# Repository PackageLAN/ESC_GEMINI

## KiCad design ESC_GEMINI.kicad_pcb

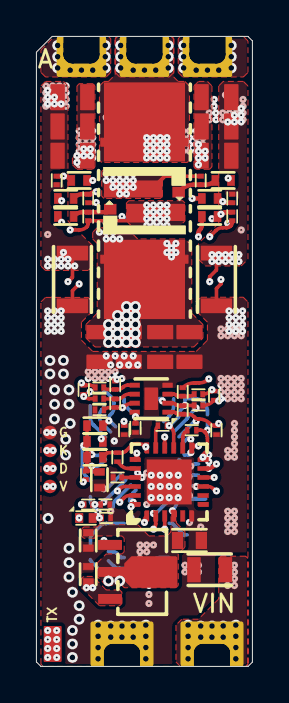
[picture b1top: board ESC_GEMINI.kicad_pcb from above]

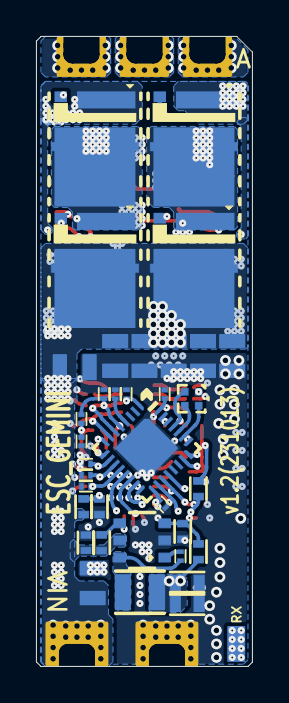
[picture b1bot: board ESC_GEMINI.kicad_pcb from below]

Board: 6 copper layers, 12.0 x 35.0 mm, 106 parts (36 on the bottom side), 57 nets.

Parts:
C1, C5, C6, C15, C48, C49: 100pF; C0201(0603M)
C2, C3, C4, C7, C8, C9, C10, C11, C12, C13, C14, C16, C24, C50, C51, C53, C54: 10uF; C0805(2012M)
C17, C19, C31, C46: 10nF; C0201(0603M)
C18, C20, C21, C22, C30, C45: 100nF; C0201(0603M)
C25, C28: 1uF; C0402(1005M)
C26: 100nF; C0402(1005M)
C33, C34, C41: 10uF; C0603(1608M)
C42, C43, C44: 1uF; C0201(0603M)
D1: NH-B1010RGBT-HF; LED-4_1010
D2: DS520-30EAA02; DFN-2_1006
L1: 22uH; MC-2520
P1: V; SMP-C_b7
P2: G; SMP-C_b7
P3: TX; SMP-Q_2510
P4: RX; SMP-Q_2510
P5: D; SMP-C_b7
P6: K; SMP-C_b7
P7, P8: Solder Pad; EGP-Q_3525
P9, P10, P11: Solder Pad; EGP-Q_2722
Q1, Q2, Q3, Q4, Q5, Q6: APG024N04G; SON-FET_6050
R1, R9, R10, R21, R22, R25, R26, R28, R29: 10k; R0201(0603M)
R2, R3, R5, R13: 11k; R0402(1005M)
R4: 680R; R0402(1005M)
R6: 0R; R0201(0603M)
R7: 1Meg; R0402(1005M)
R8, R34, R37, R38: 1k; R0201(0603M)
R11: 100k; R0402(1005M)
R12: 10k; R0402(1005M)
R14: 1k; R0402(1005M)
R15: 330R; R0402(1005M)
R16: NC/100k; R0201(0603M)
R17, R18, R19, R20, R23, R24: 5.1R; R0402(1005M)
R27, R30: 1mR; R1206(3216M)
R31: SDV2012A300C181NPTF; R0805(2012M)
R32: 510R; R0201(0603M)
R35, R36, R39, R40: 100k; R0201(0603M)
U1: AT32F413KCU7-4; QFN-32_4040
U2: GM7333; SOT-89_4525
U3: LGS5148; SOT-23-6
U4: DRV8300DRGER; QFN-24_4040
U7: GS8052; DFN-8_2020

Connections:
+3V3: C20.1, C21.1, C22.1, C28.1, C45.1, P1.PAD, R9.1, R15.1, U1.1 (Vin), U1.5 (Vin_A), U1.17 (Vin), U2.3 (Vout), U7.8 (V+)
+8V: C25.1, C33.1, C34.1, C41.1, L1.2, R11.1, U2.2 (Vin), U4.4 (Vin)
/CTRL/B: D1.2 (Cathode), U1.28 (PB5)
/CTRL/BEMF: R2.2, R3.2, R4.1, R5.2, R6.1
/CTRL/BEMF_U: C19.1, R6.2, U1.10 (PA4)
/CTRL/G: D1.3 (Cathode), U1.27 (PB4)
/CTRL/I_SNS_A: C15.1, R35.2, U1.6 (PA0), U7.7 (OUT_B)
/CTRL/I_SNS_C: C6.1, R40.2, U1.7 (PA1), U7.1 (OUT_A)
/CTRL/PHA: C44.2, P9.PAD, Q5.S (Source), Q6.D (Drain), R2.1, R28.2, U4.18 (SW_A)
/CTRL/PHB: C43.2, P10.PAD, Q3.S (Source), Q4.D (Drain), R3.1, R25.2, U4.15 (SW_B)
/CTRL/PHC: C42.2, P11.PAD, Q1.S (Source), Q2.D (Drain), R5.1, R21.2, U4.12 (SW_C)
/CTRL/PWM-AN: U1.15 (PB1), U4.1 (IN_AL)
/CTRL/PWM-AP: U1.20 (PA10), U4.22 (IN_AH)
/CTRL/PWM-BN: U1.14 (PB0), U4.2 (IN_BL)
/CTRL/PWM-BP: U1.19 (PA9), U4.23 (IN_BH)
/CTRL/PWM-CN: U1.13 (PA7), U4.3 (IN_CL)
/CTRL/PWM-CP: U1.18 (PA8), U4.24 (IN_CH)
/CTRL/PWM_IN-N: C1.1, D2.2 (Anode), U1.9 (PA3)
/CTRL/PWM_IN-P: C5.1, R32.2, U1.8 (PA2)
/CTRL/R: D1.4 (Cathode), U1.26 (PB3)
/CTRL/SWCLK: P6.PAD, U1.24 (PA14)
/CTRL/SWDIO: P5.PAD, U1.23 (PA13)
/CTRL/VBUS_SNS_U: C17.1, R13.2, R14.1, U1.11 (PA5)
/CTRL/VREF_U: C31.1, C46.1, R9.2, R10.1, R36.2, R39.2, U1.12 (PA6)
/GND_A: C14.2, C49.1, C50.2, C51.2, Q6.S (Source), R8.1, R29.2, R30.2
/GND_C: C16.2, C48.1, C53.2, C54.2, Q2.S (Source), R22.2, R27.2, R37.1
GND: C1.2, C2.2, C3.2, C4.2, C5.2, C6.2, C7.2, C8.2, C9.2, C10.2, C11.2, C12.2, C13.2, C15.2, C17.2, C18.2, C19.2, C20.2, C21.2, C22.2, C24.2, C25.2, C26.2, C28.2, C31.2, C33.2, C34.2, C41.2, C45.2, C46.2, C48.2, C49.2, P2.PAD, P8.PAD, Q4.S (Source), R1.2, R4.2, R10.2, R12.1, R14.2, R16.1, R26.2, R27.1, R30.1, R31.1, R34.1, R38.1, U1.32 (PB8), U1.EP (GND), U2.1 (GND), U3.2 (GND), U4.6 (GND), U4.EP, U7.4 (V-), U7.EP
unnamed: D1.1 (Anode), R15.2
unnamed: D2.1 (Cathode), P4.PAD
unnamed: P3.PAD, R32.1
unnamed: Q1.G (Gate), R17.2, R21.1
unnamed: Q2.G (Gate), R18.2, R22.1
unnamed: Q3.G (Gate), R19.2, R25.1
unnamed: Q4.G (Gate), R20.2, R26.1
unnamed: Q5.G (Gate), R23.2, R28.1
unnamed: Q6.G (Gate), R24.2, R29.1
unnamed: R1.1, U1.31 (BOOT0)
unnamed: C18.1, U1.4 (~RST)
unnamed: C30.1, U3.1 (BST)
unnamed: R7.2, U3.4 (EN)
unnamed: R11.2, R12.2, U3.3 (FB)
unnamed: C30.2, L1.1, U3.6 (SW)
unnamed: R24.1, U4.11 (BG_A)
unnamed: R20.1, U4.10 (BG_B)
unnamed: R18.1, U4.9 (BG_C)
unnamed: C44.1, U4.20 (BST_A)
unnamed: C43.1, U4.17 (BST_B)
unnamed: C42.1, U4.14 (BST_C)
unnamed: R16.2, U4.21 (DT)
unnamed: R23.1, U4.19 (TG_A)
unnamed: R19.1, U4.16 (TG_B)
unnamed: R17.1, U4.13 (TG_C)
unnamed: R37.2, R39.1, U7.3 (IN_A+)
unnamed: R38.2, R40.1, U7.2 (IN_A-)
unnamed: R8.2, R36.1, U7.5 (IN_B+)
unnamed: R34.2, R35.1, U7.6 (IN_B-)
VBUS: C2.1, C3.1, C4.1, C7.1, C8.1, C9.1, C10.1, C11.1, C12.1, C13.1, C14.1, C16.1, C24.1, C26.1, C50.1, C51.1, C53.1, C54.1, P7.PAD, Q1.D (Drain), Q3.D (Drain), Q5.D (Drain), R7.1, R13.1, R31.2, U3.5 (VIN)

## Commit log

2023-08-25 Update gitignore
2023-09-20 Update layout and modified sense amplifier
2023-10-19 Modified the scheme of current sensing
2024-09-04 Update before RUN
